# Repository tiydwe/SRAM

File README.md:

# SRAM from scratch
256 bytes of SRAM from discrete sot-23 mosfets built without any ICs!

I'm still working on this project!

More coming to this README eventually.

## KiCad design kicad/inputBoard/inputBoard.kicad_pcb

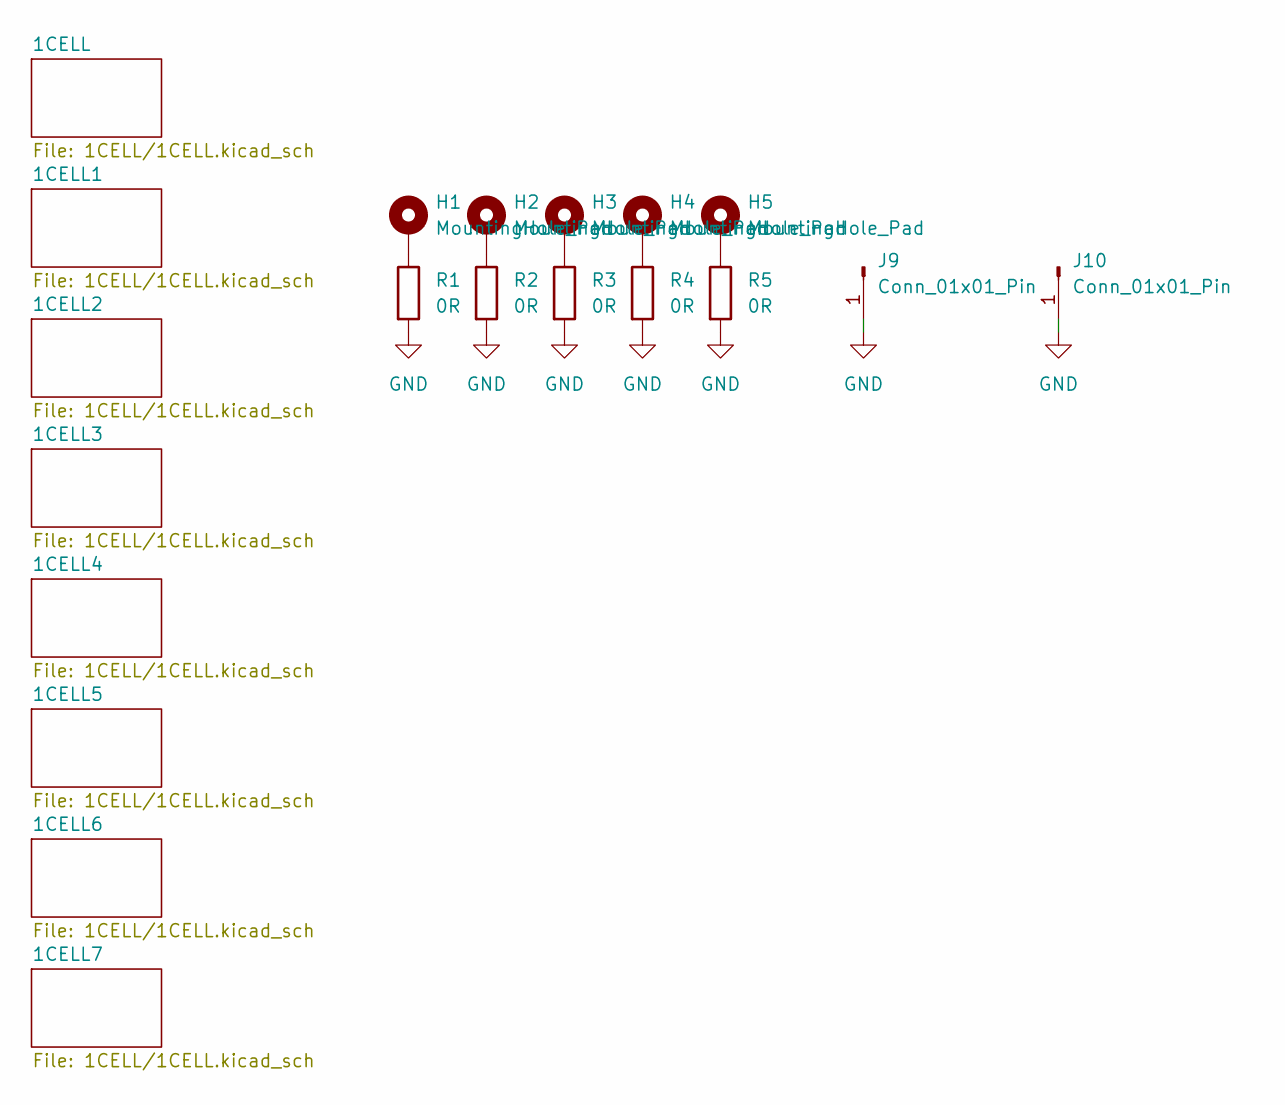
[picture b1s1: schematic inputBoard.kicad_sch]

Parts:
H1, H2, H3, H4, H5: MountingHole_Pad; MountingHole_2.2mm_M2_DIN965_Pad
J9, J10: Conn_01x01_Pin; Wire_Pad_18AWG_stranded
R1, R2, R3, R4, R5: 0R; R_1206_3216Metric_Pad1.30x1.75mm_HandSolder

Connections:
GND: J9.1 (Pin_1_1), J10.1 (Pin_1_1), R1.2, R2.2, R3.2, R4.2, R5.2; also elsewhere on the board
unnamed: H1.1 (1_1), R1.1
unnamed: H2.1 (1_1), R2.1
unnamed: H3.1 (1_1), R3.1
unnamed: H4.1 (1_1), R4.1
unnamed: H5.1 (1_1), R5.1

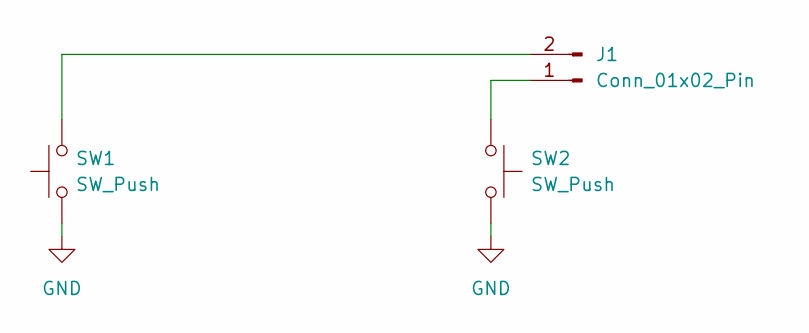
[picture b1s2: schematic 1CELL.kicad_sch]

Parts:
J1: Conn_01x02_Pin; PinHeader_1x02_P1.00mm_Vertical
SW1, SW2: SW_Push; SW_4.5mm_v2

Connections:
GND: SW1.1, SW2.2; also elsewhere on the board
unnamed: J1.1, SW2.1
unnamed: J1.2, SW1.2

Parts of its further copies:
J2, J3, J4, J5, J6, J7, J8: Conn_01x02_Pin; PinHeader_1x02_P1.00mm_Vertical
SW3, SW4, SW5, SW6, SW7, SW8, SW9, SW10, SW11, SW12, SW13, SW14, SW15, SW16: SW_Push; SW_4.5mm_v2

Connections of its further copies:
GND: SW3.1, SW4.2, SW5.1, SW6.2, SW7.1, SW8.2, SW9.1, SW10.2, SW11.1, SW12.2, SW13.1, SW14.2, SW15.1, SW16.2; also elsewhere on the board
unnamed: J2.1, SW4.1
unnamed: J2.2, SW3.2
unnamed: J3.1, SW6.1
unnamed: J3.2, SW5.2
unnamed: J4.1, SW8.1
unnamed: J4.2, SW7.2
unnamed: J5.1, SW10.1
unnamed: J5.2, SW9.2
unnamed: J6.1, SW12.1
unnamed: J6.2, SW11.2
unnamed: J7.1, SW14.1
unnamed: J7.2, SW13.2
unnamed: J8.1, SW16.1
unnamed: J8.2, SW15.2

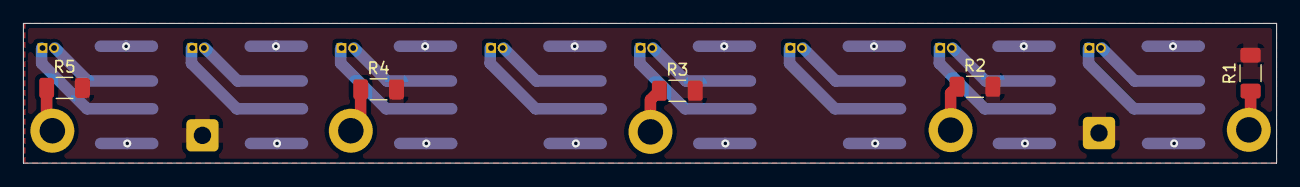
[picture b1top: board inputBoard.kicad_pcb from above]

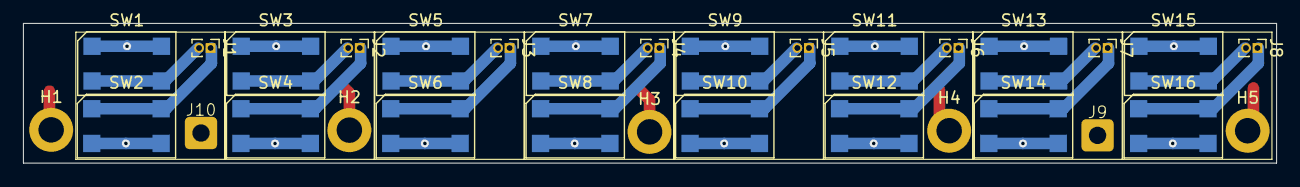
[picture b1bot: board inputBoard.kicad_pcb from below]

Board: 2 copper layers, 108.3 x 12.1 mm, 36 parts (31 on the bottom side), 22 nets.

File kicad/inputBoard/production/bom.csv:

Designator,Footprint,Quantity,Value,LCSC Part #
"J1, J2, J3, J4, J5, J6, J7, J8",PinHeader_1x02_P1.00mm_Vertical,8,Conn_01x02_Pin,
"J10, J9",Wire_Pad_18AWG_stranded,2,Conn_01x01_Pin,
"R1, R2, R3, R4, R5",1206,5,0R,
"SW1, SW10, SW11, SW12, SW13, SW14, SW15, SW16, SW2, SW3, SW4, SW5, SW6, SW7, SW8, SW9",SW_4.5mm_v2,16,SW_Push,

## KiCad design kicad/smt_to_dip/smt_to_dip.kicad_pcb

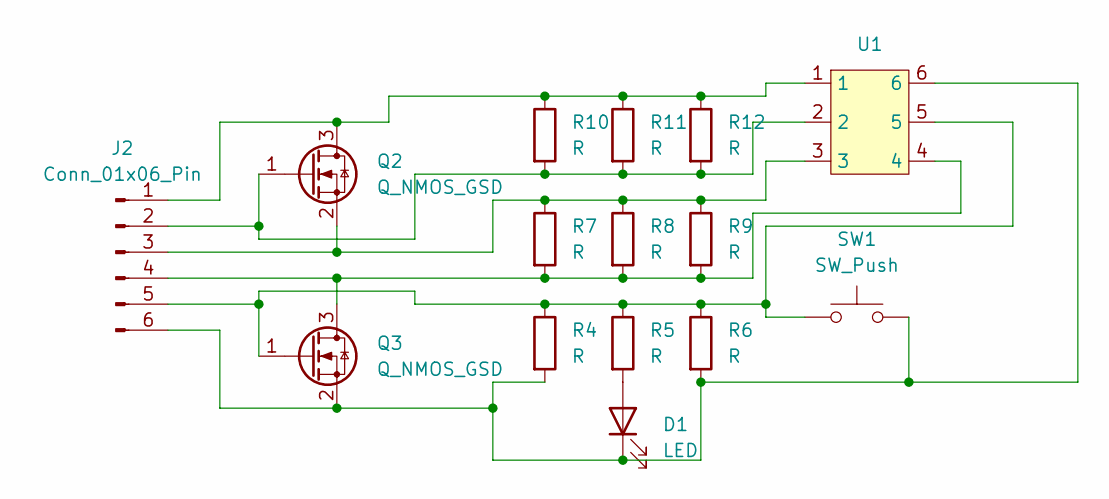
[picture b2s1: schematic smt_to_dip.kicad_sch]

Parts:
D1: LED; LED_0805_2012Metric
J2: Conn_01x06_Pin; PinHeader_1x06_P2.54mm_Vertical
Q2, Q3: Q_NMOS_GSD; SOT-23
R4, R7, R10: R; C_0603_1608Metric_Pad1.08x0.95mm_HandSolder
R5, R8, R11: R; C_0805_2012Metric_Pad1.18x1.45mm_HandSolder
R6, R9, R12: R; C_1206_3216Metric_Pad1.33x1.80mm_HandSolder
SW1: SW_Push; SW_4.5mm_v2
U1: SOT-23-6_Handsoldering

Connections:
unnamed: D1.2 (A), R5.2
unnamed: D1.1 (K), J2.6, Q3.2 (S), R4.2, R6.2, SW1.2, U1.6
unnamed: J2.1, Q2.3 (D), R10.1, R11.1, R12.1, U1.1
unnamed: J2.2, Q2.1 (G), R10.2, R11.2, R12.2, U1.2
unnamed: J2.3, Q2.2 (S), R7.1, R8.1, R9.1, U1.3
unnamed: J2.4, Q3.3 (D), R7.2, R8.2, R9.2, U1.4
unnamed: J2.5, Q3.1 (G), R4.1, R5.1, R6.1, SW1.1, U1.5

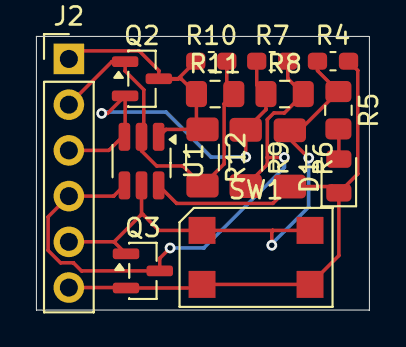
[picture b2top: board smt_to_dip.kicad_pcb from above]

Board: 2 copper layers, 18.5 x 15.2 mm, 15 parts (0 on the bottom side), 7 nets.

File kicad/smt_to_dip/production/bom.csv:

Designator,Footprint,Quantity,Value,LCSC Part #
D1,0805,1,LED,
J2,PinHeader_1x06_P2.54mm_Vertical,1,Conn_01x06_Pin,
"Q2, Q3",SOT-23,2,Q_NMOS_GSD,
"R10, R4, R7",0603,3,R,
"R11, R5, R8",0805,3,R,
"R12, R6, R9",1206,3,R,
SW1,SW_4.5mm_v2,1,SW_Push,
U1,SOT-23-6_Handsoldering,1,~,

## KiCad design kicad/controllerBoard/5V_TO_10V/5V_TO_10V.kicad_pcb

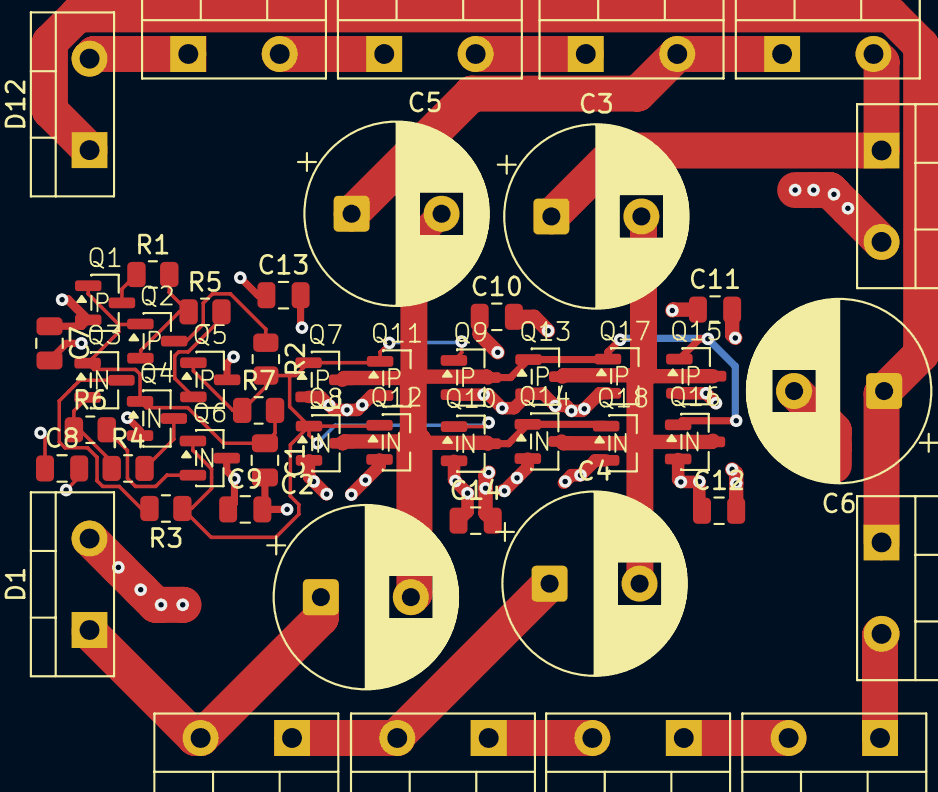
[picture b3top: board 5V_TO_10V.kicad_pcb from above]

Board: 2 copper layers, 51 parts (0 on the bottom side), 25 nets.

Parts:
C1, C7, C8, C9, C10, C11, C12, C13, C14: 100nC; C_0805_2012Metric
C2, C3, C4, C5, C6: C_Polarized; CP_Radial_D10.0mm_P5.00mm
D1, D2, D3, D4, D5, D6, D7, D8, D9, D10, D11, D12: MUR1560FAC; TO-220-2_Vertical
Q1, Q2, Q5, Q7, Q9, Q11, Q13, Q15, Q17: Q_PMOS_GSD; SOT-23-P
Q3, Q4, Q6, Q8, Q10, Q12, Q14, Q16, Q18: Q_NMOS_GSD; SOT-23-N
R1, R2, R3, R4: 47R; R_0805_2012Metric
R5, R6: 1R; R_0805_2012Metric
R7: 470R; R_0805_2012Metric

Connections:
+5V: C7.1, C8.1, C9.1, C10.1, C11.2, C12.2, C13.2, C14.2, D1.2 (A), D2.2 (A), Q1.2 (S), Q6.3 (D), Q7.2 (S), Q9.2 (S), Q11.2 (S), Q13.2 (S), Q15.2 (S), Q17.2 (S)
/10V: C6.1, D11.1 (K), D12.1 (K)
GND: C1.2, C6.2, C7.2, C8.2, C9.2, C10.2, C11.1, C12.1, C13.1, C14.1, Q4.2 (S), Q5.3 (D), Q8.2 (S), Q10.2 (S), Q12.2 (S), Q14.2 (S), Q16.2 (S), Q18.2 (S)
unnamed: C2.1, D1.1 (K), D3.2 (A)
unnamed: C3.1, D2.1 (K), D4.2 (A)
unnamed: C4.1, D3.1 (K), D5.2 (A)
unnamed: C5.1, D4.1 (K), D6.2 (A)
unnamed: D5.1 (K), D7.2 (A)
unnamed: D6.1 (K), D8.2 (A)
unnamed: D7.1 (K), D9.2 (A)
unnamed: D8.1 (K), D10.2 (A)
unnamed: D10.1 (K), D12.2 (A)
unnamed: D9.1 (K), D11.2 (A)
unnamed: Q1.3 (D), R1.1
unnamed: C1.1, Q1.1 (G), Q2.1 (G), Q3.1 (G), Q4.1 (G), R7.2
unnamed: Q2.3 (D), R2.1
unnamed: Q2.2 (S), R1.2, R5.1
unnamed: Q3.3 (D), R3.2
unnamed: Q3.2 (S), R4.1, R6.1
unnamed: Q4.3 (D), R4.2
unnamed: Q5.2 (S), R5.2
unnamed: Q6.2 (S), R6.2
unnamed: C2.2, C5.2, Q7.3 (D), Q8.3 (D), Q9.3 (D), Q10.3 (D), Q11.3 (D), Q12.3 (D), Q13.1 (G), Q14.1 (G), Q15.1 (G), Q16.1 (G), Q17.1 (G), Q18.1 (G)
unnamed: Q5.1 (G), Q6.1 (G), Q7.1 (G), Q8.1 (G), Q9.1 (G), Q10.1 (G), Q11.1 (G), Q12.1 (G), R2.2, R3.1, R7.1
unnamed: C3.2, C4.2, Q13.3 (D), Q14.3 (D), Q15.3 (D), Q16.3 (D), Q17.3 (D), Q18.3 (D)

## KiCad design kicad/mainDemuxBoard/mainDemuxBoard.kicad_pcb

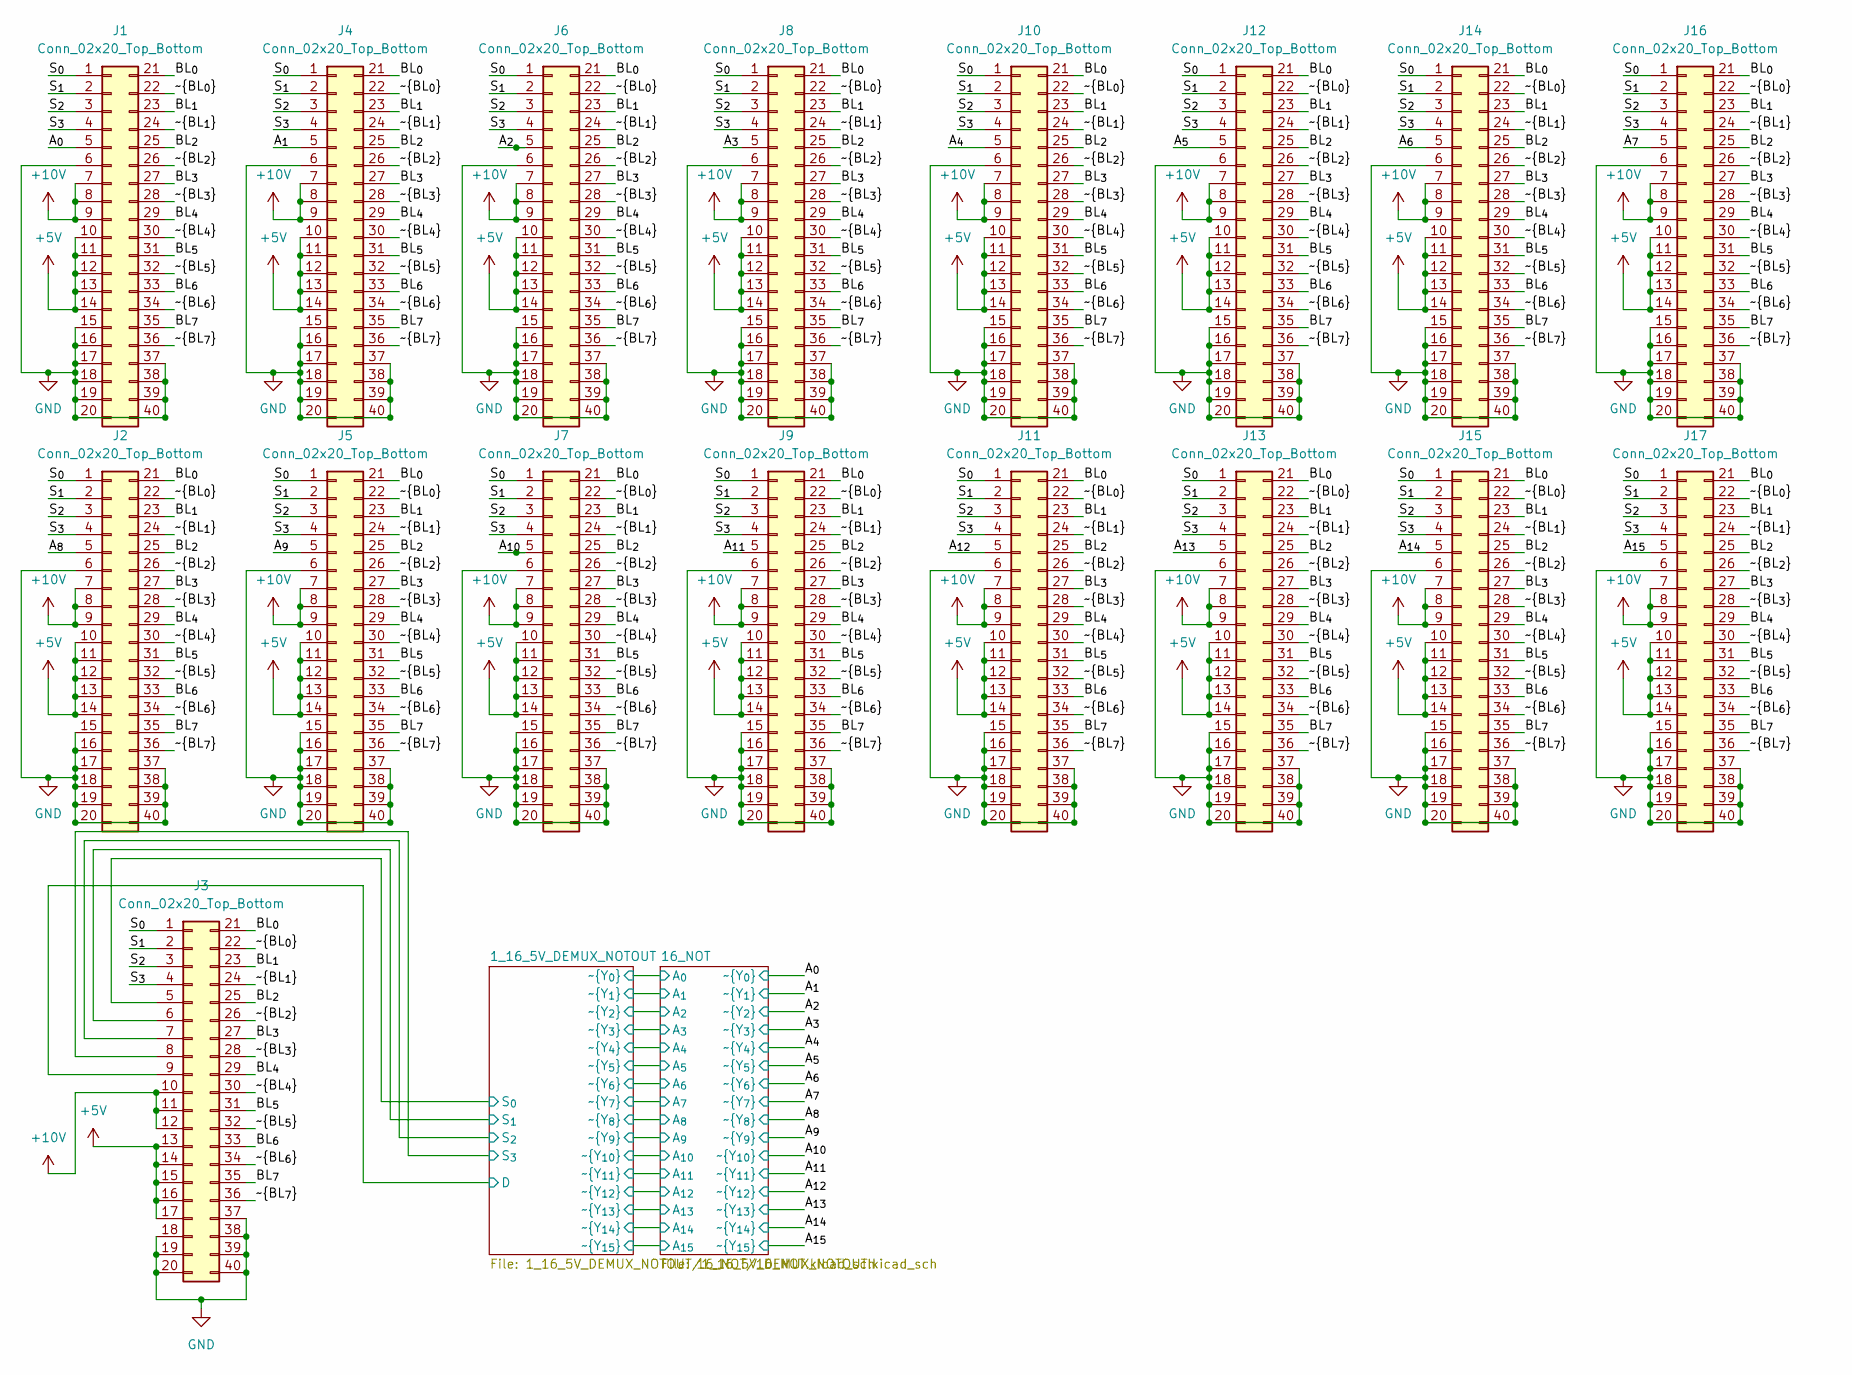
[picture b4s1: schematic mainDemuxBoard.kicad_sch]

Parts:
J1, J2, J3, J4, J5, J6, J7, J8, J9, J10, J11, J12, J13, J14, J15, J16, J17: Conn_02x20_Top_Bottom; IDC-Header_2x20_P2.54mm_Latch_Vertical

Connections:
+5V: J1.10, J1.11, J1.12, J1.13, J1.14, J2.10, J2.11, J2.12, J2.13, J2.14, J3.13, J3.14, J3.15, J3.16, J3.17, J4.10, J4.11, J4.12, J4.13, J4.14, J5.10, J5.11, J5.12, J5.13, J5.14, J6.10, J6.11, J6.12, J6.13, J6.14, J7.10, J7.11, J7.12, J7.13, J7.14, J8.10, J8.11, J8.12, J8.13, J8.14, J9.10, J9.11, J9.12, J9.13, J9.14, J10.10, J10.11, J10.12, J10.13, J10.14, J11.10, J11.11, J11.12, J11.13, J11.14, J12.10, J12.11, J12.12, J12.13, J12.14, J13.10, J13.11, J13.12, J13.13, J13.14, J14.10, J14.11, J14.12, J14.13, J14.14, J15.10, J15.11, J15.12, J15.13, J15.14, J16.10, J16.11, J16.12, J16.13, J16.14, J17.10, J17.11, J17.12, J17.13, J17.14; also elsewhere on the board
+10V: J1.7, J1.8, J1.9, J2.7, J2.8, J2.9, J3.10, J3.11, J3.12, J4.7, J4.8, J4.9, J5.7, J5.8, J5.9, J6.7, J6.8, J6.9, J7.7, J7.8, J7.9, J8.7, J8.8, J8.9, J9.7, J9.8, J9.9, J10.7, J10.8, J10.9, J11.7, J11.8, J11.9, J12.7, J12.8, J12.9, J13.7, J13.8, J13.9, J14.7, J14.8, J14.9, J15.7, J15.8, J15.9, J16.7, J16.8, J16.9, J17.7, J17.8, J17.9
/1_16_5V_DEMUX_NOTOUT/D: J3.9; also elsewhere on the board
/1_16_5V_DEMUX_NOTOUT/S_{0}: J3.5; also elsewhere on the board
/1_16_5V_DEMUX_NOTOUT/S_{1}: J3.6; also elsewhere on the board
/1_16_5V_DEMUX_NOTOUT/S_{2}: J3.7; also elsewhere on the board
/1_16_5V_DEMUX_NOTOUT/S_{3}: J3.8; also elsewhere on the board
/A_{0}: J1.5; also elsewhere on the board
/A_{1}: J4.5; also elsewhere on the board
/A_{2}: J6.5; also elsewhere on the board
/A_{3}: J8.5; also elsewhere on the board
/A_{4}: J10.5; also elsewhere on the board
/A_{5}: J12.5; also elsewhere on the board
/A_{6}: J14.5; also elsewhere on the board
/A_{7}: J16.5; also elsewhere on the board
/A_{8}: J2.5; also elsewhere on the board
/A_{9}: J5.5; also elsewhere on the board
/A_{10}: J7.5; also elsewhere on the board
/A_{11}: J9.5; also elsewhere on the board
/A_{12}: J11.5; also elsewhere on the board
/A_{13}: J13.5; also elsewhere on the board
/A_{14}: J15.5; also elsewhere on the board
/A_{15}: J17.5; also elsewhere on the board
/BL_{0}: J1.21, J2.21, J3.21, J4.21, J5.21, J6.21, J7.21, J8.21, J9.21, J10.21, J11.21, J12.21, J13.21, J14.21, J15.21, J16.21, J17.21
/BL_{1}: J1.23, J2.23, J3.23, J4.23, J5.23, J6.23, J7.23, J8.23, J9.23, J10.23, J11.23, J12.23, J13.23, J14.23, J15.23, J16.23, J17.23
/BL_{2}: J1.25, J2.25, J3.25, J4.25, J5.25, J6.25, J7.25, J8.25, J9.25, J10.25, J11.25, J12.25, J13.25, J14.25, J15.25, J16.25, J17.25
/BL_{3}: J1.27, J2.27, J3.27, J4.27, J5.27, J6.27, J7.27, J8.27, J9.27, J10.27, J11.27, J12.27, J13.27, J14.27, J15.27, J16.27, J17.27
/BL_{4}: J1.29, J2.29, J3.29, J4.29, J5.29, J6.29, J7.29, J8.29, J9.29, J10.29, J11.29, J12.29, J13.29, J14.29, J15.29, J16.29, J17.29
/BL_{5}: J1.31, J2.31, J3.31, J4.31, J5.31, J6.31, J7.31, J8.31, J9.31, J10.31, J11.31, J12.31, J13.31, J14.31, J15.31, J16.31, J17.31
/BL_{6}: J1.33, J2.33, J3.33, J4.33, J5.33, J6.33, J7.33, J8.33, J9.33, J10.33, J11.33, J12.33, J13.33, J14.33, J15.33, J16.33, J17.33
/BL_{7}: J1.35, J2.35, J3.35, J4.35, J5.35, J6.35, J7.35, J8.35, J9.35, J10.35, J11.35, J12.35, J13.35, J14.35, J15.35, J16.35, J17.35
/S_{0}: J1.1, J2.1, J3.1, J4.1, J5.1, J6.1, J7.1, J8.1, J9.1, J10.1, J11.1, J12.1, J13.1, J14.1, J15.1, J16.1, J17.1
/S_{1}: J1.2, J2.2, J3.2, J4.2, J5.2, J6.2, J7.2, J8.2, J9.2, J10.2, J11.2, J12.2, J13.2, J14.2, J15.2, J16.2, J17.2
/S_{2}: J1.3, J2.3, J3.3, J4.3, J5.3, J6.3, J7.3, J8.3, J9.3, J10.3, J11.3, J12.3, J13.3, J14.3, J15.3, J16.3, J17.3
/S_{3}: J1.4, J2.4, J3.4, J4.4, J5.4, J6.4, J7.4, J8.4, J9.4, J10.4, J11.4, J12.4, J13.4, J14.4, J15.4, J16.4, J17.4
/~BL_{0}: J1.22, J2.22, J3.22, J4.22, J5.22, J6.22, J7.22, J8.22, J9.22, J10.22, J11.22, J12.22, J13.22, J14.22, J15.22, J16.22, J17.22
/~BL_{1}: J1.24, J2.24, J3.24, J4.24, J5.24, J6.24, J7.24, J8.24, J9.24, J10.24, J11.24, J12.24, J13.24, J14.24, J15.24, J16.24, J17.24
/~BL_{2}: J1.26, J2.26, J3.26, J4.26, J5.26, J6.26, J7.26, J8.26, J9.26, J10.26, J11.26, J12.26, J13.26, J14.26, J15.26, J16.26, J17.26
/~BL_{3}: J1.28, J2.28, J3.28, J4.28, J5.28, J6.28, J7.28, J8.28, J9.28, J10.28, J11.28, J12.28, J13.28, J14.28, J15.28, J16.28, J17.28
/~BL_{4}: J1.30, J2.30, J3.30, J4.30, J5.30, J6.30, J7.30, J8.30, J9.30, J10.30, J11.30, J12.30, J13.30, J14.30, J15.30, J16.30, J17.30
/~BL_{5}: J1.32, J2.32, J3.32, J4.32, J5.32, J6.32, J7.32, J8.32, J9.32, J10.32, J11.32, J12.32, J13.32, J14.32, J15.32, J16.32, J17.32
/~BL_{6}: J1.34, J2.34, J3.34, J4.34, J5.34, J6.34, J7.34, J8.34, J9.34, J10.34, J11.34, J12.34, J13.34, J14.34, J15.34, J16.34, J17.34
/~BL_{7}: J1.36, J2.36, J3.36, J4.36, J5.36, J6.36, J7.36, J8.36, J9.36, J10.36, J11.36, J12.36, J13.36, J14.36, J15.36, J16.36, J17.36
GND: J1.6, J1.15, J1.16, J1.17, J1.18, J1.19, J1.20, J1.37, J1.38, J1.39, J1.40, J2.6, J2.15, J2.16, J2.17, J2.18, J2.19, J2.20, J2.37, J2.38, J2.39, J2.40, J3.18, J3.19, J3.20, J3.37, J3.38, J3.39, J3.40, J4.6, J4.15, J4.16, J4.17, J4.18, J4.19, J4.20, J4.37, J4.38, J4.39, J4.40, J5.6, J5.15, J5.16, J5.17, J5.18, J5.19, J5.20, J5.37, J5.38, J5.39, J5.40, J6.6, J6.15, J6.16, J6.17, J6.18, J6.19, J6.20, J6.37, J6.38, J6.39, J6.40, J7.6, J7.15, J7.16, J7.17, J7.18, J7.19, J7.20, J7.37, J7.38, J7.39, J7.40, J8.6, J8.15, J8.16, J8.17, J8.18, J8.19, J8.20, J8.37, J8.38, J8.39, J8.40, J9.6, J9.15, J9.16, J9.17, J9.18, J9.19, J9.20, J9.37, J9.38, J9.39, J9.40, J10.6, J10.15, J10.16, J10.17, J10.18, J10.19, J10.20, J10.37, J10.38, J10.39, J10.40, J11.6, J11.15, J11.16, J11.17, J11.18, J11.19, J11.20, J11.37, J11.38, J11.39, J11.40, J12.6, J12.15, J12.16, J12.17, J12.18, J12.19, J12.20, J12.37, J12.38, J12.39, J12.40, J13.6, J13.15, J13.16, J13.17, J13.18, J13.19, J13.20, J13.37, J13.38, J13.39, J13.40, J14.6, J14.15, J14.16, J14.17, J14.18, J14.19, J14.20, J14.37, J14.38, J14.39, J14.40, J15.6, J15.15, J15.16, J15.17, J15.18, J15.19, J15.20, J15.37, J15.38, J15.39, J15.40, J16.6, J16.15, J16.16, J16.17, J16.18, J16.19, J16.20, J16.37, J16.38, J16.39, J16.40, J17.6, J17.15, J17.16, J17.17, J17.18, J17.19, J17.20, J17.37, J17.38, J17.39, J17.40; also elsewhere on the board

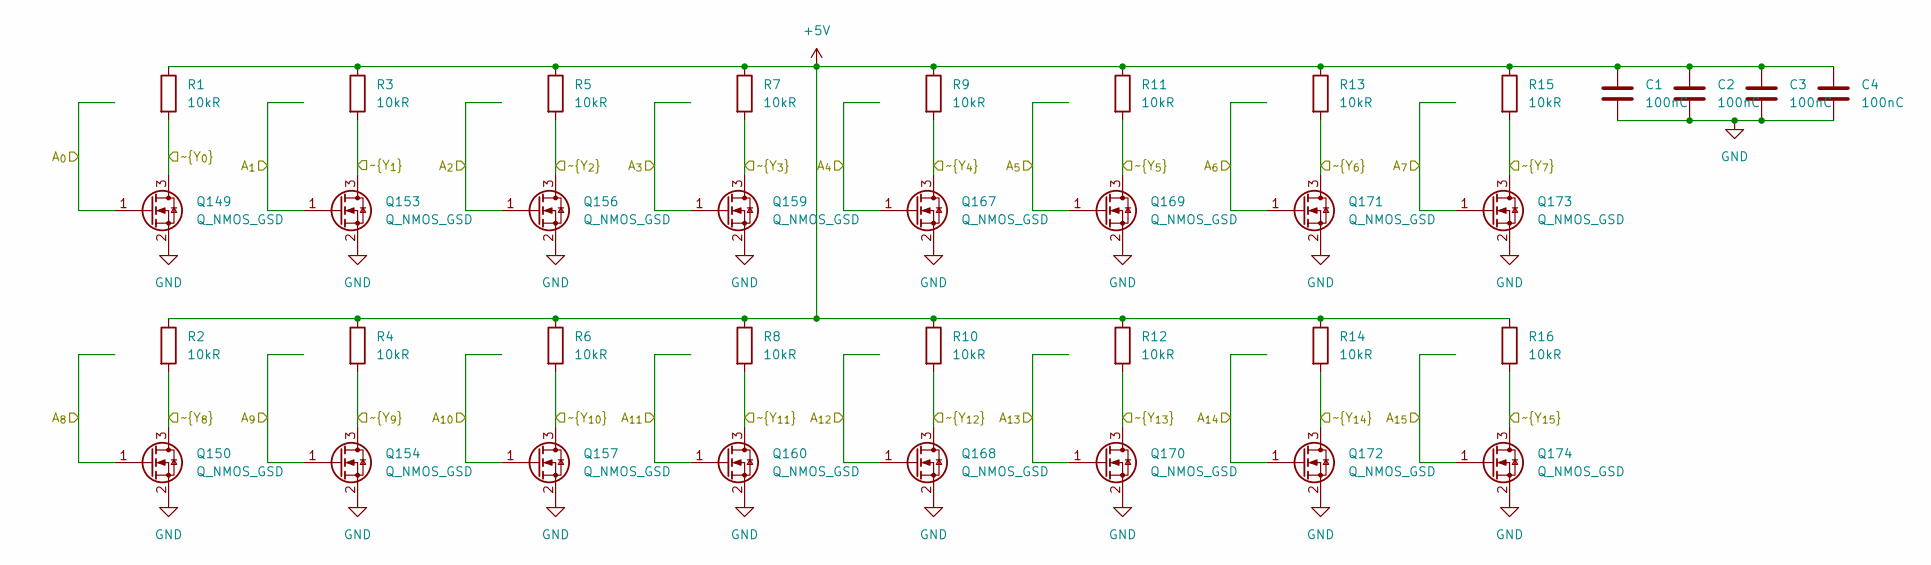
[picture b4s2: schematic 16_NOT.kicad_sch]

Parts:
C1, C2, C3, C4: 100nC; C_0603_1608Metric
Q149, Q150, Q153, Q154, Q156, Q157, Q159, Q160, Q167, Q168, Q169, Q170, Q171, Q172, Q173, Q174: Q_NMOS_GSD; SOT-23-N; LCSC Part # C49308282
R1, R2, R3, R4, R5, R6, R7, R8, R9, R10, R11, R12, R13, R14, R15, R16: 10kR; R_0603_1608Metric; LCSC Part # C54920960

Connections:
+5V: C1.1, C2.1, C3.1, C4.1, R1.1, R2.1, R3.1, R4.1, R5.1, R6.1, R7.1, R8.1, R9.1, R10.1, R11.1, R12.1, R13.1, R14.1, R15.1, R16.1; also elsewhere on the board
/16_NOT/A_{0}: Q149.1 (G); also elsewhere on the board
/16_NOT/A_{1}: Q153.1 (G); also elsewhere on the board
/16_NOT/A_{2}: Q156.1 (G); also elsewhere on the board
/16_NOT/A_{3}: Q159.1 (G); also elsewhere on the board
/16_NOT/A_{4}: Q167.1 (G); also elsewhere on the board
/16_NOT/A_{5}: Q169.1 (G); also elsewhere on the board
/16_NOT/A_{6}: Q171.1 (G); also elsewhere on the board
/16_NOT/A_{7}: Q173.1 (G); also elsewhere on the board
/16_NOT/A_{8}: Q150.1 (G); also elsewhere on the board
/16_NOT/A_{9}: Q154.1 (G); also elsewhere on the board
/16_NOT/A_{10}: Q157.1 (G); also elsewhere on the board
/16_NOT/A_{11}: Q160.1 (G); also elsewhere on the board
/16_NOT/A_{12}: Q168.1 (G); also elsewhere on the board
/16_NOT/A_{13}: Q170.1 (G); also elsewhere on the board
/16_NOT/A_{14}: Q172.1 (G); also elsewhere on the board
/16_NOT/A_{15}: Q174.1 (G); also elsewhere on the board
/A_{0}: Q149.3 (D), R1.2; also elsewhere on the board
/A_{1}: Q153.3 (D), R3.2; also elsewhere on the board
/A_{2}: Q156.3 (D), R5.2; also elsewhere on the board
/A_{3}: Q159.3 (D), R7.2; also elsewhere on the board
/A_{4}: Q167.3 (D), R9.2; also elsewhere on the board
/A_{5}: Q169.3 (D), R11.2; also elsewhere on the board
/A_{6}: Q171.3 (D), R13.2; also elsewhere on the board
/A_{7}: Q173.3 (D), R15.2; also elsewhere on the board
/A_{8}: Q150.3 (D), R2.2; also elsewhere on the board
/A_{9}: Q154.3 (D), R4.2; also elsewhere on the board
/A_{10}: Q157.3 (D), R6.2; also elsewhere on the board
/A_{11}: Q160.3 (D), R8.2; also elsewhere on the board
/A_{12}: Q168.3 (D), R10.2; also elsewhere on the board
/A_{13}: Q170.3 (D), R12.2; also elsewhere on the board
/A_{14}: Q172.3 (D), R14.2; also elsewhere on the board
/A_{15}: Q174.3 (D), R16.2; also elsewhere on the board
GND: C1.2, C2.2, C3.2, C4.2, Q149.2 (S), Q150.2 (S), Q153.2 (S), Q154.2 (S), Q156.2 (S), Q157.2 (S), Q159.2 (S), Q160.2 (S), Q167.2 (S), Q168.2 (S), Q169.2 (S), Q170.2 (S), Q171.2 (S), Q172.2 (S), Q173.2 (S), Q174.2 (S); also elsewhere on the board

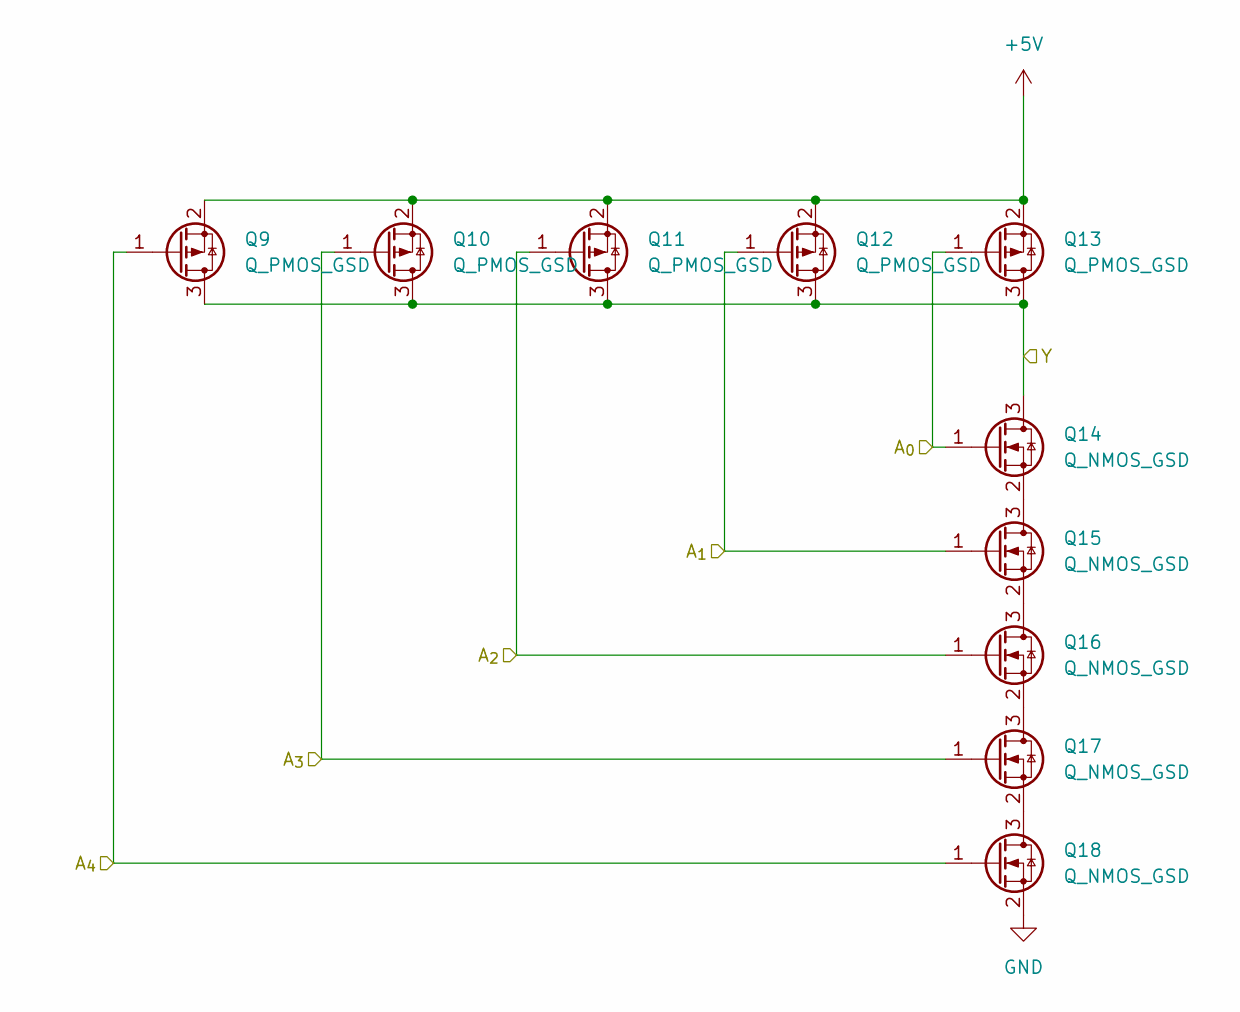
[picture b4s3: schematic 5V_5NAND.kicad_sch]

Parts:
Q9, Q10, Q11, Q12, Q13: Q_PMOS_GSD; SOT-23-P; LCSC Part # C41384537
Q14, Q15, Q16, Q17, Q18: Q_NMOS_GSD; SOT-23-N; LCSC Part # C49308282

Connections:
+5V: Q9.2 (S), Q10.2 (S), Q11.2 (S), Q12.2 (S), Q13.2 (S); also elsewhere on the board
/1_16_5V_DEMUX_NOTOUT/5VNOT1/Y: Q11.1 (G), Q16.1 (G); also elsewhere on the board
/1_16_5V_DEMUX_NOTOUT/5VNOT2/Y: Q10.1 (G), Q17.1 (G); also elsewhere on the board
/1_16_5V_DEMUX_NOTOUT/5VNOT3/Y: Q9.1 (G), Q18.1 (G); also elsewhere on the board
/1_16_5V_DEMUX_NOTOUT/5VNOT/Y: Q12.1 (G), Q15.1 (G); also elsewhere on the board
/1_16_5V_DEMUX_NOTOUT/D: Q13.1 (G), Q14.1 (G); also elsewhere on the board
/16_NOT/A_{0}: Q9.3 (D), Q10.3 (D), Q11.3 (D), Q12.3 (D), Q13.3 (D), Q14.3 (D); also elsewhere on the board
GND: Q18.2 (S); also elsewhere on the board
unnamed: Q14.2 (S), Q15.3 (D)
unnamed: Q15.2 (S), Q16.3 (D)
unnamed: Q16.2 (S), Q17.3 (D)
unnamed: Q17.2 (S), Q18.3 (D)

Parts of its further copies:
Q19, Q20, Q21, Q22, Q23, Q29, Q30, Q31, Q32, Q33, Q39, Q40, Q41, Q42, Q43, Q49, Q50, Q51, Q52, Q53, Q59, Q60, Q61, Q62, Q63, Q69, Q70, Q71, Q72, Q73, Q79, Q80, Q81, Q82, Q83, Q89, Q90, Q91, Q92, Q93, Q99, Q100, Q101, Q102, Q103, Q109, Q110, Q111, Q112, Q113, Q119, Q120, Q121, Q122, Q123, Q129, Q130, Q131, Q132, Q133, Q139, Q140, Q141, Q142, Q143, Q151, Q152, Q155, Q161, Q175, Q176, Q177, Q178, Q179: Q_PMOS_GSD; SOT-23-P; LCSC Part # C41384537
Q24, Q25, Q26, Q27, Q28, Q34, Q35, Q36, Q37, Q38, Q44, Q45, Q46, Q47, Q48, Q54, Q55, Q56, Q57, Q58, Q64, Q65, Q66, Q67, Q68, Q74, Q75, Q76, Q77, Q78, Q84, Q85, Q86, Q87, Q88, Q94, Q95, Q96, Q97, Q98, Q104, Q105, Q106, Q107, Q108, Q114, Q115, Q116, Q117, Q118, Q124, Q125, Q126, Q127, Q128, Q134, Q135, Q136, Q137, Q138, Q144, Q145, Q146, Q147, Q148, Q164, Q165, Q166, Q180, Q181, Q182, Q183, Q184: Q_NMOS_GSD; SOT-23-N; LCSC Part # C49308282

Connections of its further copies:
+5V: Q19.2 (S), Q20.2 (S), Q21.2 (S), Q22.2 (S), Q23.2 (S), Q29.2 (S), Q30.2 (S), Q31.2 (S), Q32.2 (S), Q33.2 (S), Q39.2 (S), Q40.2 (S), Q41.2 (S), Q42.2 (S), Q43.2 (S), Q49.2 (S), Q50.2 (S), Q51.2 (S), Q52.2 (S), Q53.2 (S), Q59.2 (S), Q60.2 (S), Q61.2 (S), Q62.2 (S), Q63.2 (S), Q69.2 (S), Q70.2 (S), Q71.2 (S), Q72.2 (S), Q73.2 (S), Q79.2 (S), Q80.2 (S), Q81.2 (S), Q82.2 (S), Q83.2 (S), Q89.2 (S), Q90.2 (S), Q91.2 (S), Q92.2 (S), Q93.2 (S), Q99.2 (S), Q100.2 (S), Q101.2 (S), Q102.2 (S), Q103.2 (S), Q109.2 (S), Q110.2 (S), Q111.2 (S), Q112.2 (S), Q113.2 (S), Q119.2 (S), Q120.2 (S), Q121.2 (S), Q122.2 (S), Q123.2 (S), Q129.2 (S), Q130.2 (S), Q131.2 (S), Q132.2 (S), Q133.2 (S), Q139.2 (S), Q140.2 (S), Q141.2 (S), Q142.2 (S), Q143.2 (S), Q151.2 (S), Q152.2 (S), Q155.2 (S), Q161.2 (S), Q175.2 (S), Q176.2 (S), Q177.2 (S), Q178.2 (S), Q179.2 (S); also elsewhere on the board
/1_16_5V_DEMUX_NOTOUT/5VNOT1/Y: Q21.1 (G), Q26.1 (G), Q31.1 (G), Q36.1 (G), Q41.1 (G), Q46.1 (G), Q51.1 (G), Q56.1 (G), Q61.1 (G), Q66.1 (G), Q71.1 (G), Q76.1 (G), Q81.1 (G), Q86.1 (G); also elsewhere on the board
/1_16_5V_DEMUX_NOTOUT/5VNOT2/Y: Q20.1 (G), Q27.1 (G), Q30.1 (G), Q37.1 (G), Q40.1 (G), Q47.1 (G), Q90.1 (G), Q97.1 (G), Q100.1 (G), Q107.1 (G), Q110.1 (G), Q117.1 (G), Q120.1 (G), Q127.1 (G); also elsewhere on the board
/1_16_5V_DEMUX_NOTOUT/5VNOT3/Y: Q19.1 (G), Q28.1 (G), Q49.1 (G), Q58.1 (G), Q59.1 (G), Q68.1 (G), Q89.1 (G), Q98.1 (G), Q99.1 (G), Q108.1 (G), Q129.1 (G), Q138.1 (G), Q139.1 (G), Q148.1 (G); also elsewhere on the board
/1_16_5V_DEMUX_NOTOUT/5VNOT/Y: Q32.1 (G), Q35.1 (G), Q52.1 (G), Q55.1 (G), Q72.1 (G), Q75.1 (G), Q92.1 (G), Q95.1 (G), Q112.1 (G), Q115.1 (G), Q132.1 (G), Q135.1 (G); also elsewhere on the board
/1_16_5V_DEMUX_NOTOUT/D: Q23.1 (G), Q24.1 (G), Q33.1 (G), Q34.1 (G), Q43.1 (G), Q44.1 (G), Q53.1 (G), Q54.1 (G), Q63.1 (G), Q64.1 (G), Q73.1 (G), Q74.1 (G), Q83.1 (G), Q84.1 (G), Q93.1 (G), Q94.1 (G), Q103.1 (G), Q104.1 (G), Q113.1 (G), Q114.1 (G), Q123.1 (G), Q124.1 (G), Q133.1 (G), Q134.1 (G), Q143.1 (G), Q144.1 (G), Q161.1 (G), Q179.1 (G), Q180.1 (G); also elsewhere on the board
/1_16_5V_DEMUX_NOTOUT/S_{0}: Q22.1 (G), Q25.1 (G), Q42.1 (G), Q45.1 (G), Q62.1 (G), Q65.1 (G), Q82.1 (G), Q85.1 (G), Q102.1 (G), Q105.1 (G), Q122.1 (G), Q125.1 (G), Q142.1 (G), Q145.1 (G), Q178.1 (G), Q181.1 (G); also elsewhere on the board
/1_16_5V_DEMUX_NOTOUT/S_{1}: Q91.1 (G), Q96.1 (G), Q101.1 (G), Q106.1 (G), Q111.1 (G), Q116.1 (G), Q121.1 (G), Q126.1 (G), Q131.1 (G), Q136.1 (G), Q141.1 (G), Q146.1 (G), Q155.1 (G), Q164.1 (G), Q177.1 (G), Q182.1 (G); also elsewhere on the board
/1_16_5V_DEMUX_NOTOUT/S_{2}: Q50.1 (G), Q57.1 (G), Q60.1 (G), Q67.1 (G), Q70.1 (G), Q77.1 (G), Q80.1 (G), Q87.1 (G), Q130.1 (G), Q137.1 (G), Q140.1 (G), Q147.1 (G), Q152.1 (G), Q165.1 (G), Q176.1 (G), Q183.1 (G); also elsewhere on the board
/1_16_5V_DEMUX_NOTOUT/S_{3}: Q29.1 (G), Q38.1 (G), Q39.1 (G), Q48.1 (G), Q69.1 (G), Q78.1 (G), Q79.1 (G), Q88.1 (G), Q109.1 (G), Q118.1 (G), Q119.1 (G), Q128.1 (G), Q151.1 (G), Q166.1 (G), Q175.1 (G), Q184.1 (G); also elsewhere on the board
/16_NOT/A_{1}: Q29.3 (D), Q30.3 (D), Q31.3 (D), Q32.3 (D), Q33.3 (D), Q34.3 (D); also elsewhere on the board
/16_NOT/A_{2}: Q49.3 (D), Q50.3 (D), Q51.3 (D), Q52.3 (D), Q53.3 (D), Q54.3 (D); also elsewhere on the board
/16_NOT/A_{3}: Q69.3 (D), Q70.3 (D), Q71.3 (D), Q72.3 (D), Q73.3 (D), Q74.3 (D); also elsewhere on the board
/16_NOT/A_{4}: Q89.3 (D), Q90.3 (D), Q91.3 (D), Q92.3 (D), Q93.3 (D), Q94.3 (D); also elsewhere on the board
/16_NOT/A_{5}: Q109.3 (D), Q110.3 (D), Q111.3 (D), Q112.3 (D), Q113.3 (D), Q114.3 (D); also elsewhere on the board
/16_NOT/A_{6}: Q129.3 (D), Q130.3 (D), Q131.3 (D), Q132.3 (D), Q133.3 (D), Q134.3 (D); also elsewhere on the board
/16_NOT/A_{7}: Q151.3 (D), Q152.3 (D), Q155.3 (D), Q161.3 (D); also elsewhere on the board
/16_NOT/A_{8}: Q19.3 (D), Q20.3 (D), Q21.3 (D), Q22.3 (D), Q23.3 (D), Q24.3 (D); also elsewhere on the board
/16_NOT/A_{9}: Q39.3 (D), Q40.3 (D), Q41.3 (D), Q42.3 (D), Q43.3 (D), Q44.3 (D); also elsewhere on the board
/16_NOT/A_{10}: Q59.3 (D), Q60.3 (D), Q61.3 (D), Q62.3 (D), Q63.3 (D), Q64.3 (D); also elsewhere on the board
/16_NOT/A_{11}: Q79.3 (D), Q80.3 (D), Q81.3 (D), Q82.3 (D), Q83.3 (D), Q84.3 (D); also elsewhere on the board
/16_NOT/A_{12}: Q99.3 (D), Q100.3 (D), Q101.3 (D), Q102.3 (D), Q103.3 (D), Q104.3 (D); also elsewhere on the board
/16_NOT/A_{13}: Q119.3 (D), Q120.3 (D), Q121.3 (D), Q122.3 (D), Q123.3 (D), Q124.3 (D); also elsewhere on the board
/16_NOT/A_{14}: Q139.3 (D), Q140.3 (D), Q141.3 (D), Q142.3 (D), Q143.3 (D), Q144.3 (D); also elsewhere on the board
/16_NOT/A_{15}: Q175.3 (D), Q176.3 (D), Q177.3 (D), Q178.3 (D), Q179.3 (D), Q180.3 (D); also elsewhere on the board
GND: Q28.2 (S), Q38.2 (S), Q48.2 (S), Q58.2 (S), Q68.2 (S), Q78.2 (S), Q88.2 (S), Q98.2 (S), Q108.2 (S), Q118.2 (S), Q128.2 (S), Q138.2 (S), Q148.2 (S), Q166.2 (S), Q184.2 (S); also elsewhere on the board
unnamed: Q24.2 (S), Q25.3 (D)
unnamed: Q25.2 (S), Q26.3 (D)
unnamed: Q26.2 (S), Q27.3 (D)
unnamed: Q27.2 (S), Q28.3 (D)
unnamed: Q34.2 (S), Q35.3 (D)
unnamed: Q35.2 (S), Q36.3 (D)
unnamed: Q36.2 (S), Q37.3 (D)
unnamed: Q37.2 (S), Q38.3 (D)
unnamed: Q44.2 (S), Q45.3 (D)
unnamed: Q45.2 (S), Q46.3 (D)
unnamed: Q46.2 (S), Q47.3 (D)
unnamed: Q47.2 (S), Q48.3 (D)
unnamed: Q54.2 (S), Q55.3 (D)
unnamed: Q55.2 (S), Q56.3 (D)
unnamed: Q56.2 (S), Q57.3 (D)
unnamed: Q57.2 (S), Q58.3 (D)
unnamed: Q64.2 (S), Q65.3 (D)
unnamed: Q65.2 (S), Q66.3 (D)
unnamed: Q66.2 (S), Q67.3 (D)
unnamed: Q67.2 (S), Q68.3 (D)
unnamed: Q74.2 (S), Q75.3 (D)
unnamed: Q75.2 (S), Q76.3 (D)
unnamed: Q76.2 (S), Q77.3 (D)
unnamed: Q77.2 (S), Q78.3 (D)
unnamed: Q84.2 (S), Q85.3 (D)
unnamed: Q85.2 (S), Q86.3 (D)
unnamed: Q86.2 (S), Q87.3 (D)
unnamed: Q87.2 (S), Q88.3 (D)
unnamed: Q94.2 (S), Q95.3 (D)
unnamed: Q95.2 (S), Q96.3 (D)
unnamed: Q96.2 (S), Q97.3 (D)
unnamed: Q97.2 (S), Q98.3 (D)
unnamed: Q104.2 (S), Q105.3 (D)
unnamed: Q105.2 (S), Q106.3 (D)
unnamed: Q106.2 (S), Q107.3 (D)
unnamed: Q107.2 (S), Q108.3 (D)
unnamed: Q114.2 (S), Q115.3 (D)
unnamed: Q115.2 (S), Q116.3 (D)
unnamed: Q116.2 (S), Q117.3 (D)
unnamed: Q117.2 (S), Q118.3 (D)
unnamed: Q124.2 (S), Q125.3 (D)
unnamed: Q125.2 (S), Q126.3 (D)
unnamed: Q126.2 (S), Q127.3 (D)
unnamed: Q127.2 (S), Q128.3 (D)
unnamed: Q134.2 (S), Q135.3 (D)
unnamed: Q135.2 (S), Q136.3 (D)
unnamed: Q136.2 (S), Q137.3 (D)
unnamed: Q137.2 (S), Q138.3 (D)
unnamed: Q144.2 (S), Q145.3 (D)
unnamed: Q145.2 (S), Q146.3 (D)
unnamed: Q146.2 (S), Q147.3 (D)
unnamed: Q147.2 (S), Q148.3 (D)
unnamed 121: Q164.3 (D); also elsewhere on the board
unnamed: Q164.2 (S), Q165.3 (D)
unnamed: Q165.2 (S), Q166.3 (D)
unnamed: Q180.2 (S), Q181.3 (D)
unnamed: Q181.2 (S), Q182.3 (D)
unnamed: Q182.2 (S), Q183.3 (D)
unnamed: Q183.2 (S), Q184.3 (D)

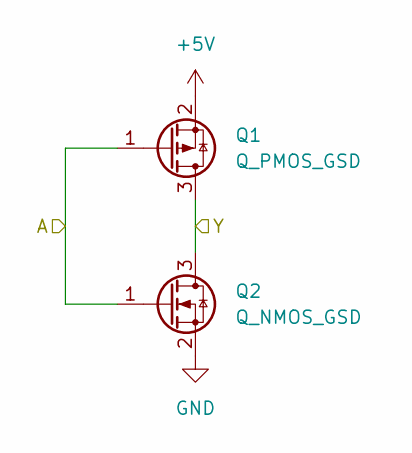
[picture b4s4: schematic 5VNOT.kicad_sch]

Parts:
Q1: Q_PMOS_GSD; SOT-23-P; LCSC Part # C41384537
Q2: Q_NMOS_GSD; SOT-23-N; LCSC Part # C49308282

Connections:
+5V: Q1.2 (S); also elsewhere on the board
/1_16_5V_DEMUX_NOTOUT/5VNOT/Y: Q1.3 (D), Q2.3 (D); also elsewhere on the board
/1_16_5V_DEMUX_NOTOUT/S_{0}: Q1.1 (G), Q2.1 (G); also elsewhere on the board
GND: Q2.2 (S); also elsewhere on the board

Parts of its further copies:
Q3, Q5, Q7: Q_PMOS_GSD; SOT-23-P; LCSC Part # C41384537
Q4, Q6, Q8: Q_NMOS_GSD; SOT-23-N; LCSC Part # C49308282

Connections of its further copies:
+5V: Q3.2 (S), Q5.2 (S), Q7.2 (S); also elsewhere on the board
/1_16_5V_DEMUX_NOTOUT/5VNOT1/Y: Q3.3 (D), Q4.3 (D); also elsewhere on the board
/1_16_5V_DEMUX_NOTOUT/5VNOT2/Y: Q5.3 (D), Q6.3 (D); also elsewhere on the board
/1_16_5V_DEMUX_NOTOUT/5VNOT3/Y: Q7.3 (D), Q8.3 (D); also elsewhere on the board
/1_16_5V_DEMUX_NOTOUT/S_{1}: Q3.1 (G), Q4.1 (G); also elsewhere on the board
/1_16_5V_DEMUX_NOTOUT/S_{2}: Q5.1 (G), Q6.1 (G); also elsewhere on the board
/1_16_5V_DEMUX_NOTOUT/S_{3}: Q7.1 (G), Q8.1 (G); also elsewhere on the board
GND: Q4.2 (S), Q6.2 (S), Q8.2 (S); also elsewhere on the board
